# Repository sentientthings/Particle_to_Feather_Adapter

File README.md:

# Particle_to_Feather_Adapter
Adapt Particle Photon or Electron to Adafruit Feather header

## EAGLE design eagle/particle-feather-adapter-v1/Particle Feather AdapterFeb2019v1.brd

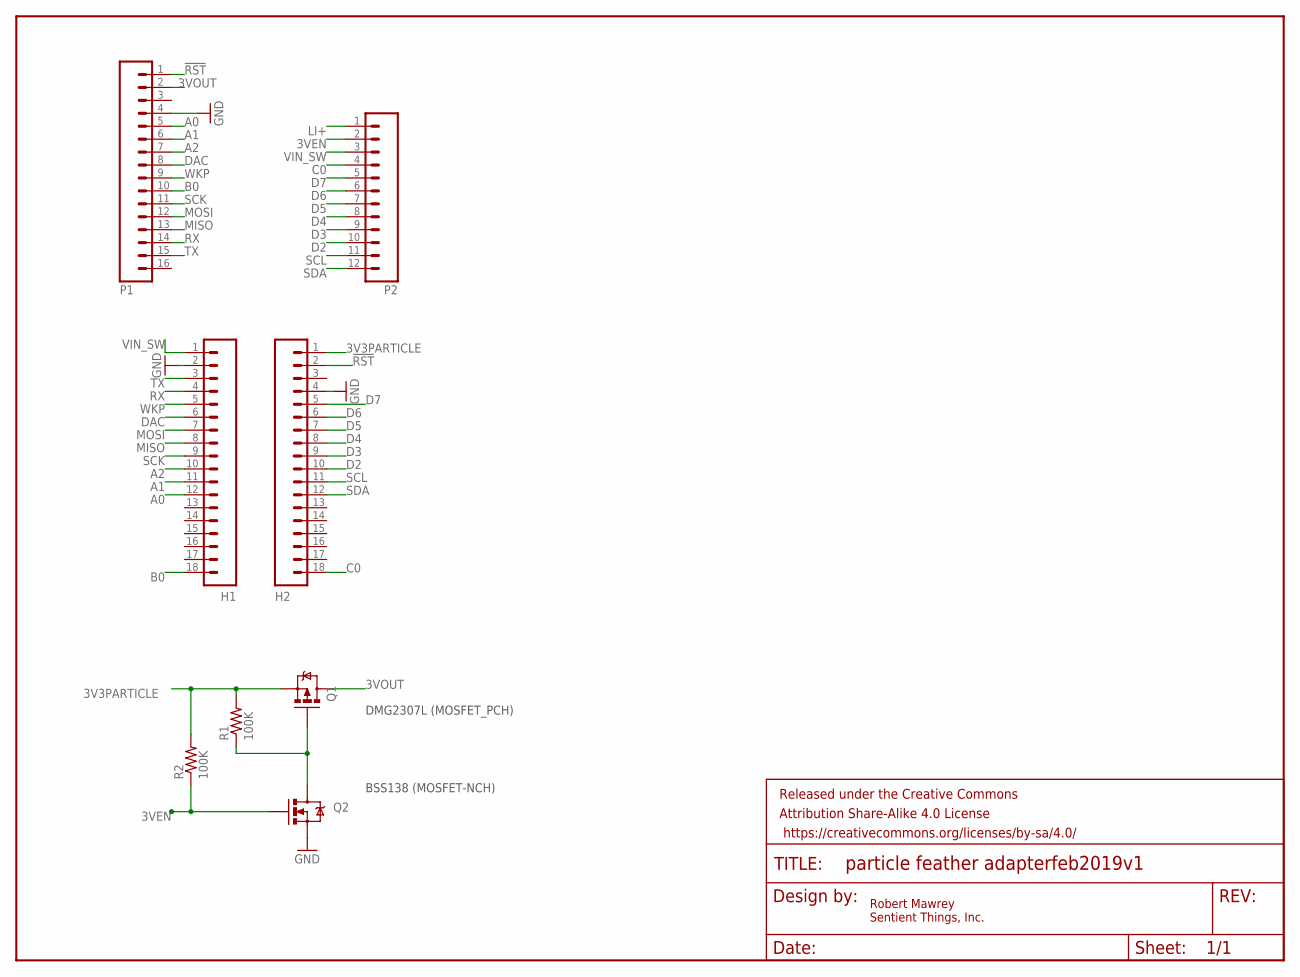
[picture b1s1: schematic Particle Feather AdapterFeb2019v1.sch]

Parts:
FRAME1, FRAME2: FRAME-LETTER; CREATIVE_COMMONS; PARTNO DNP
H1, H2: M18-MILLMAX; 1X18-01SMD; PARTNO 310-43-118-41-105000
P1: M16-FEATHER; 1X16-01SMDRIGHT; PARTNO 68016-116HLF
P2: M12-FEATHER; 1X12-01SMDLEFT; PARTNO 68016-212HLF
Q1: MOSFET-PCHANNELSMD; SOT23-3; PARTNO DMG2307L-7
Q2: MOSFET-NCHANNELSMD; MAWREY_SOT23-3; PARTNO BSS138
R1, R2: 100K; 0603-RES; PARTNO RC0603JR-07100KL

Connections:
3V3PARTICLE: H2.1, Q1.2 (S), R1.2, R2.2
3VEN: P2.2, Q2.1 (G), R2.1
3VOUT: P1.2, Q1.3 (D)
!RST: H2.2, P1.1
A0: H1.12, P1.5
A1: H1.11, P1.6
A2: H1.10, P1.7
B0: H1.18, P1.10
C0: H2.18, P2.4
D2: H2.10, P2.10
D3: H2.9, P2.9
D4: H2.8, P2.8
D5: H2.7, P2.7
D6: H2.6, P2.6
D7: H2.5, P2.5
DAC: H1.6, P1.8
GND: H1.2, H2.4, P1.4, Q2.2 (S)
LI+: P2.1
MISO: H1.8, P1.13
MOSI: H1.7, P1.12
unnamed: Q1.1 (G), Q2.3 (D), R1.1
RX: H1.4, P1.14
SCK: H1.9, P1.11
SCL: H2.11, P2.11
SDA: H2.12, P2.12
TX: H1.3, P1.15
VIN_SW: H1.1, P2.3
WKP: H1.5, P1.9

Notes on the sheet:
DMG2307L (MOSFET_PCH)
BSS138 (MOSFET-NCH)
Robert Mawrey Sentient Things, Inc.

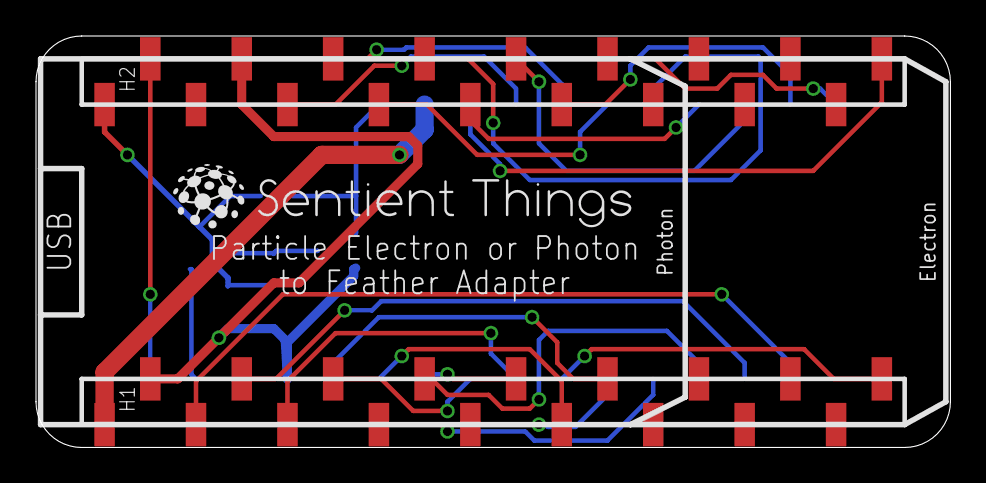
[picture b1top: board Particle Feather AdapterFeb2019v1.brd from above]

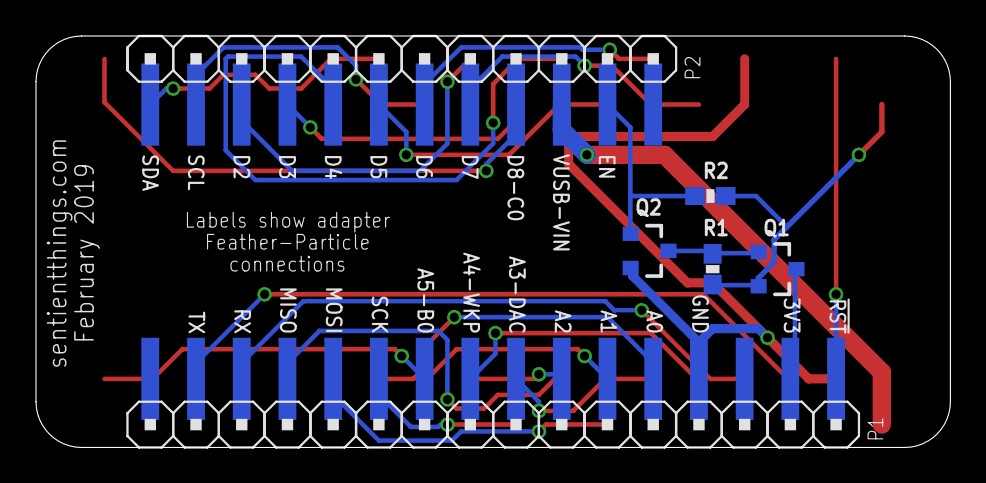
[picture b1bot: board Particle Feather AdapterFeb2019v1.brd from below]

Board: 2 copper layers, 50.8 x 22.9 mm, 11 parts (6 on the bottom side), 27 nets.

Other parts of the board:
U$1: SENTIENT_THINGS

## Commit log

2019-05-21 Eagle files
2019-05-21 License

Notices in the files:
parts and their libraries:
Mawrey: Released under the Creative Commons Attribution Share-Alike 4.0 License
Mawrey: https://creativecommons.org/licenses/by-sa/4.0
Mawrey: Released under the Creative Commons
